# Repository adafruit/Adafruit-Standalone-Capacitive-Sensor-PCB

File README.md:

# Adafruit Standalone Capacitive Sensor PCBs

&nbsp; 
&nbsp; 
<br />

Breakout boards for stand-alone capacitive touch sensors. These are the simplest ways to create projects with capacitive touch. No microcontroller is required here - just power with 1.8 to 5.5VDC. When a capacitive load is detected (e.g. a person touches one of the conductive contacts) the corresponding LED lights up and the output pin goes low. 

Format is EagleCAD schematic and board layout

For more details, check out the product pages at

-----> http://www.adafruit.com/products/1362

-----> http://www.adafruit.com/products/1374

-----> http://www.adafruit.com/products/1375

### License

Adafruit invests time and resources providing this open source design, please support Adafruit and open-source hardware by purchasing products from [Adafruit](https://www.adafruit.com)!

All text above must be included in any redistribution

Designed by Limor Fried/Ladyada for Adafruit Industries.
Creative Commons Attribution/Share-Alike, all text above must be included in any redistribution. 
See license.txt for additional information.

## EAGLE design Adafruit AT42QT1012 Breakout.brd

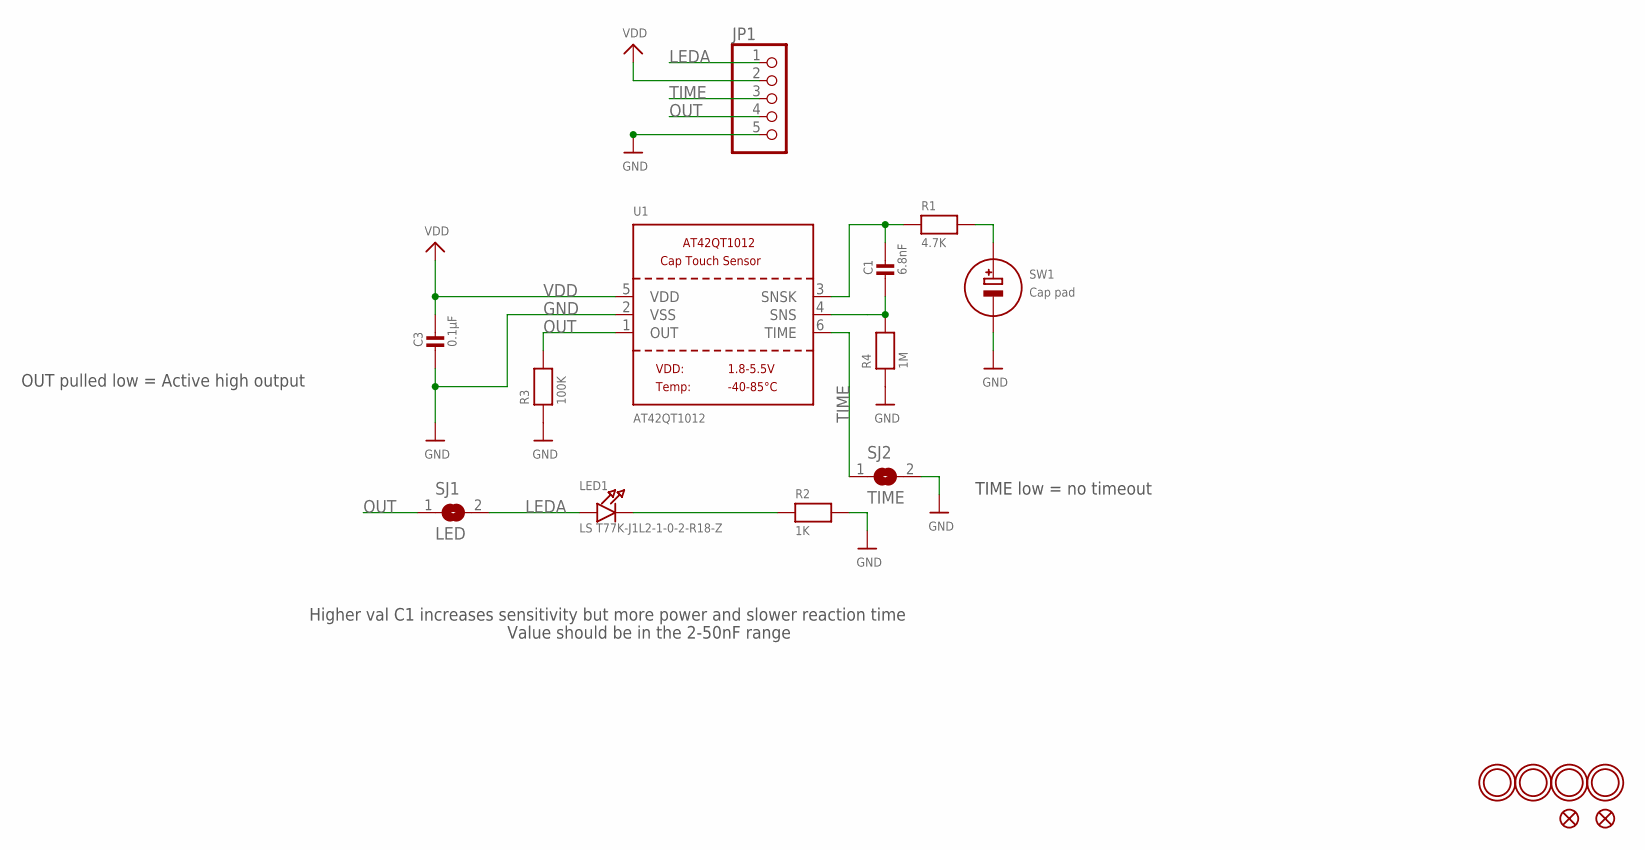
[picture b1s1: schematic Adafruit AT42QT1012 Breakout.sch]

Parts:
C1: 6.8nF; _0805
C3: 0.1µF; _0805
FID1, FID2: FIDUCIAL""; FIDUCIAL_1MM
JP1: HEADER-1X570MIL; 1X05_ROUND_70
LED1: LS T77K-J1L2-1-0-2-R18-Z; PLCC2_REVMOUNT
R1: 4.7K; _0805
R2: 1K; _0805
R3: 100K; _0805
R4: 1M; _0805
SJ1: LED; SOLDERJUMPER_CLOSEDWIRE
SJ2: TIME; SOLDERJUMPER_CLOSEDWIRE
SW1: Cap pad; CAPTOUCH_SIMPLE_12.5MM
U1: AT42QT1012; SOT23-6
U$6, U$9, U$10, U$11: MOUNTINGHOLE2.5; MOUNTINGHOLE_2.5_PLATED

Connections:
GND: C3.2, JP1.5, R2.2, R3.1, R4.1, SJ2.2, SW1.G (-), U1.2 (VSS)
LEDA: JP1.1, LED1.A, SJ1.2
unnamed: R1.2, SW1.E (+)
unnamed: C1.2, R4.2, U1.4 (SNS)
unnamed: C1.1, R1.1, U1.3 (SNSK)
unnamed: LED1.K (C), R2.1
OUT: JP1.4, R3.2, SJ1.1, U1.1 (OUT)
TIME: JP1.3, SJ2.1, U1.6 (TIME)
VDD: C3.1, JP1.2, U1.5 (VDD)

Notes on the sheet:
Higher val C1 increases sensitivity but more power and slower reaction time
Value should be in the 2-50nF range
OUT pulled low = Active high output
TIME low = no timeout

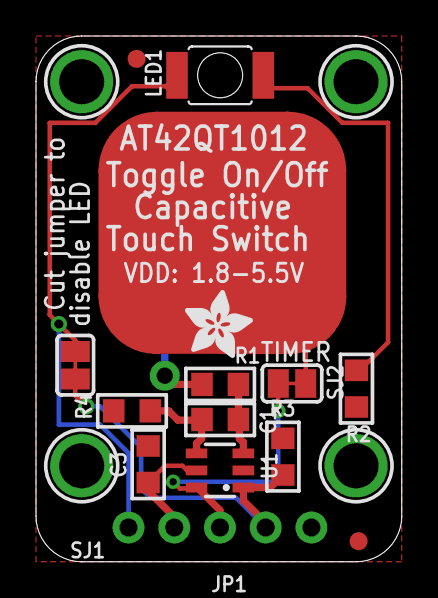
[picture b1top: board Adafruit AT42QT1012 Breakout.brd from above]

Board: 2 copper layers, 20.3 x 29.2 mm, 19 parts (1 on the bottom side), 9 nets.

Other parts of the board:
U$12: ADAFRUIT_3.5MM

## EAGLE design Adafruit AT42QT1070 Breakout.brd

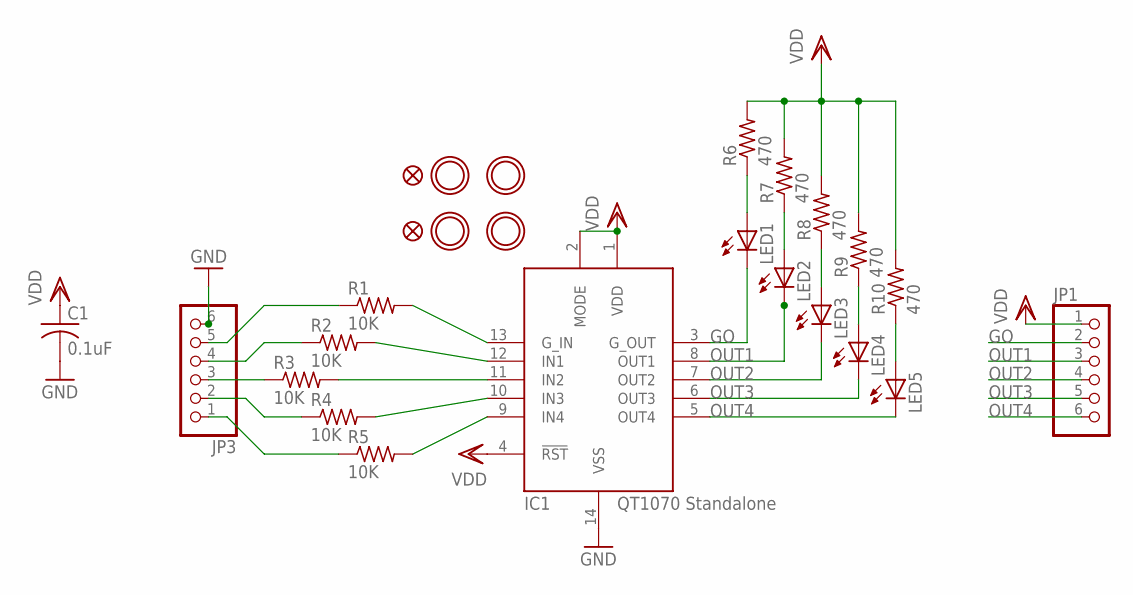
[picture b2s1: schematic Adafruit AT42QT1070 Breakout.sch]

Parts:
C1: 0.1uF; C0805K
FID1, FID2: FIDUCIAL""; FIDUCIAL_1MM
IC1: AT42QT1070-SSU; SO14
JP1, JP3: PINHD-1X6CB; 1X06-CLEANBIG
LED1, LED2, LED3, LED4, LED5: LEDCHIP-LED0805; CHIP-LED0805
R1, R2, R3, R4, R5: 10K; R0805
R6, R7, R8, R9, R10: 470; R0805
U$1, U$2, U$3, U$4: MOUNTINGHOLE2.5; MOUNTINGHOLE_2.5_PLATED

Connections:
GND: C1.2, IC1.14 (VSS), JP3.6
GO: IC1.3 (G_OUT), JP1.2, LED1.C
unnamed: IC1.13 (G_IN), R1.2
unnamed: IC1.12 (IN1), R2.2
unnamed: IC1.11 (IN2), R3.2
unnamed: IC1.10 (IN3), R4.2
unnamed: IC1.9 (IN4), R5.2
unnamed: JP3.5, R1.1
unnamed: JP3.4, R2.1
unnamed: JP3.3, R3.1
unnamed: JP3.2, R4.1
unnamed: JP3.1, R5.1
unnamed: LED1.A, R6.1
unnamed: LED2.A, R7.1
unnamed: LED3.A, R8.1
unnamed: LED4.A, R9.1
unnamed: LED5.A, R10.1
OUT1: IC1.8 (OUT1), JP1.3, LED2.C
OUT2: IC1.7 (OUT2), JP1.4, LED3.C
OUT3: IC1.6 (OUT3), JP1.5, LED4.C
OUT4: IC1.5 (OUT4), JP1.6, LED5.C
VDD: C1.1, IC1.1 (VDD), IC1.2 (MODE), IC1.4 (!RST), JP1.1, R6.2, R7.2, R8.2, R9.2, R10.2

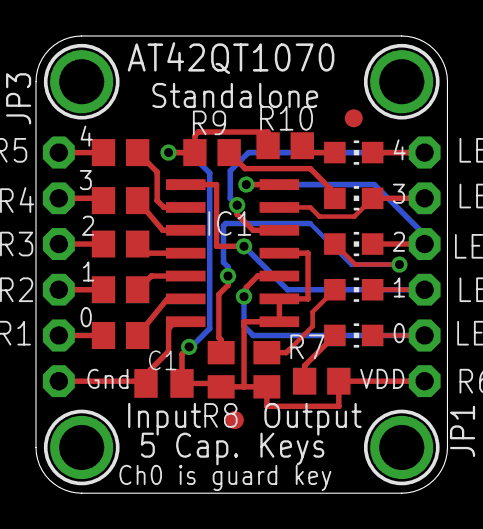
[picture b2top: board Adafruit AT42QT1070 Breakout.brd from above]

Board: 2 copper layers, 22.9 x 25.4 mm, 26 parts (1 on the bottom side), 22 nets.

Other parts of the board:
U$6: ADAFRUIT_5MM

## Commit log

2015-01-26 init

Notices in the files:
parts and their libraries:
microbuilder: This work is placed in the public domain, and may be freely used for commercial and non-commercial work with the following conditions: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
